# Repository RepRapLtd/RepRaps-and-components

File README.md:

# RepRaps-and-components
Various designs for RepRaps and bits of them

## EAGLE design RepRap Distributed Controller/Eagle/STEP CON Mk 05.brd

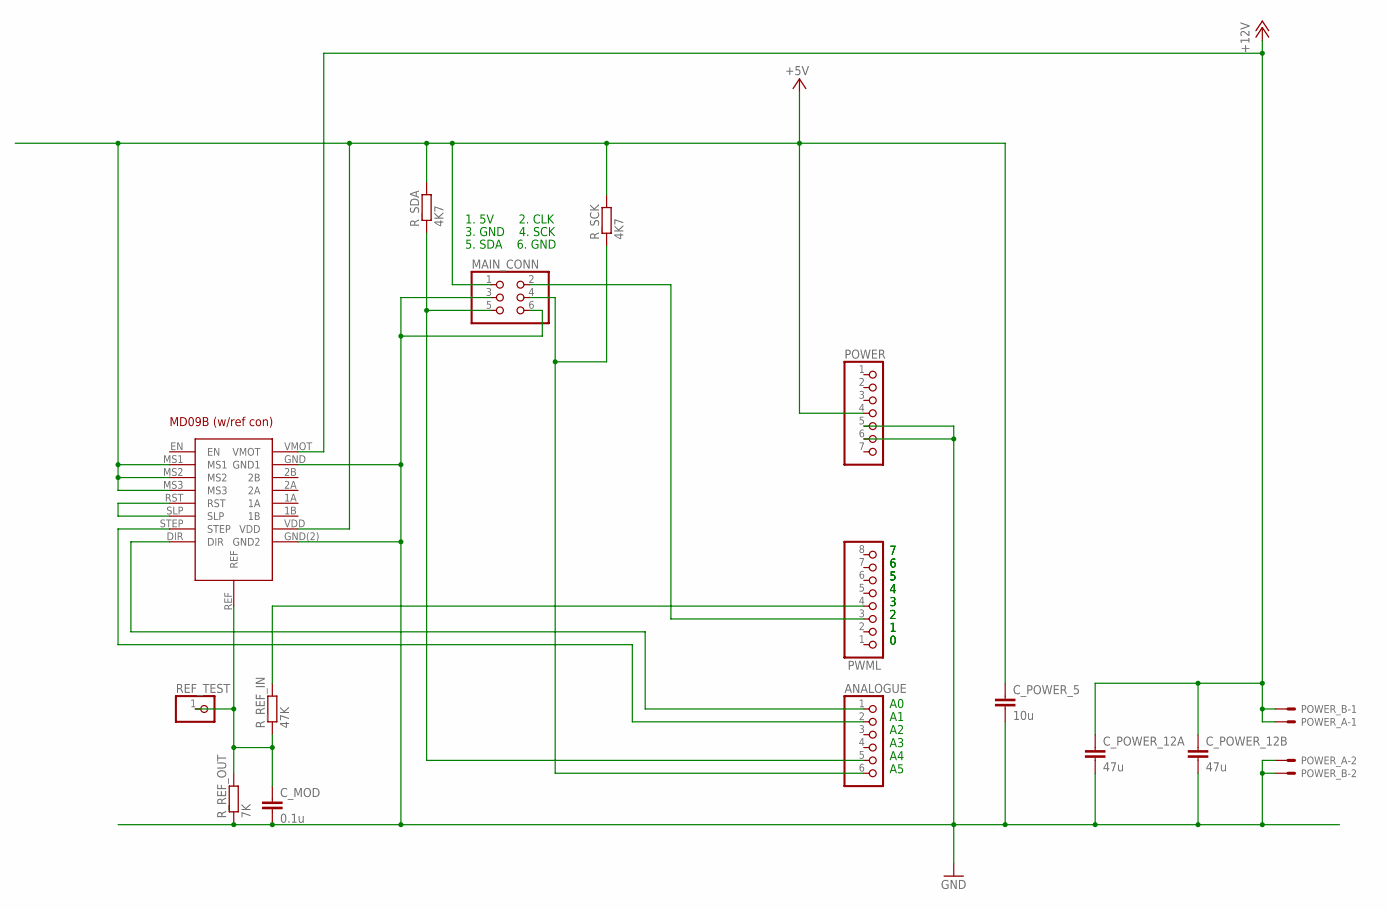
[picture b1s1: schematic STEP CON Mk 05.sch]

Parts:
ANALOGUE: PINHD-1X6; 1X06
C_MOD: 0.1u; C1206
C_POWER_5: 10u; C1206
C_POWER_12A, C_POWER_12B: 47u; C1206
MAIN_CONN: PINHD-2X3; 2X03
POWER: PINHD-1X7; 1X07
POWER_A: KK-156-2
POWER_B: KK-156-2
PWML: PINHD-1X8; 1X08
REF_TEST: PINHD-1X1; 1X01
R_REF_IN: 47K; M0805
R_REF_OUT: 7K; M0805
R_SCK: 4K7; M0805
R_SDA: 4K7; M0805
U$1: MD09B_MOD_LP; MD90B_MOD_LP

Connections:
+5V: C_POWER_5.1, MAIN_CONN.1, POWER.4, R_SCK.2, R_SDA.2, U$1.MS1, U$1.MS2, U$1.MS3, U$1.VDD
+12V: C_POWER_12A.1, C_POWER_12B.1, POWER_A.1, POWER_B.1, U$1.VMOT
DIR: ANALOGUE.1, U$1.DIR
GND: C_MOD.2, C_POWER_5.2, C_POWER_12A.2, C_POWER_12B.2, MAIN_CONN.3, MAIN_CONN.6, POWER.5, POWER.6, POWER_A.2, POWER_B.2, R_REF_OUT.1, U$1.GND (GND1), U$1.GND(2) (GND2)
PWM: PWML.4, R_REF_IN.2
REF1: C_MOD.1, REF_TEST.1, R_REF_IN.1, R_REF_OUT.2, U$1.REF
SCK: ANALOGUE.6, MAIN_CONN.4, R_SCK.1
SDA: ANALOGUE.5, MAIN_CONN.5, R_SDA.1
SKYCLOCK: MAIN_CONN.2, PWML.3
SLP-RST: U$1.RST, U$1.SLP
STEP: ANALOGUE.2, U$1.STEP

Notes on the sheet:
1. 5V 2. CLK 3. GND 4. SCK 5. SDA 6. GND
A0 A1 A2 A3 A4 A5

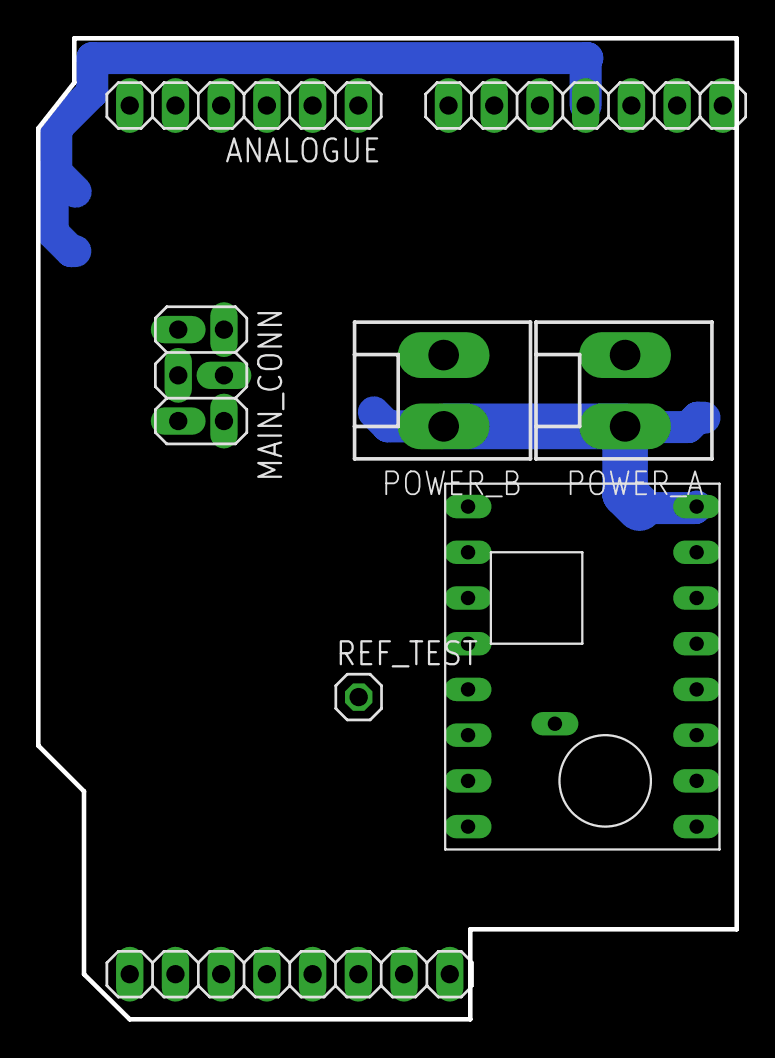
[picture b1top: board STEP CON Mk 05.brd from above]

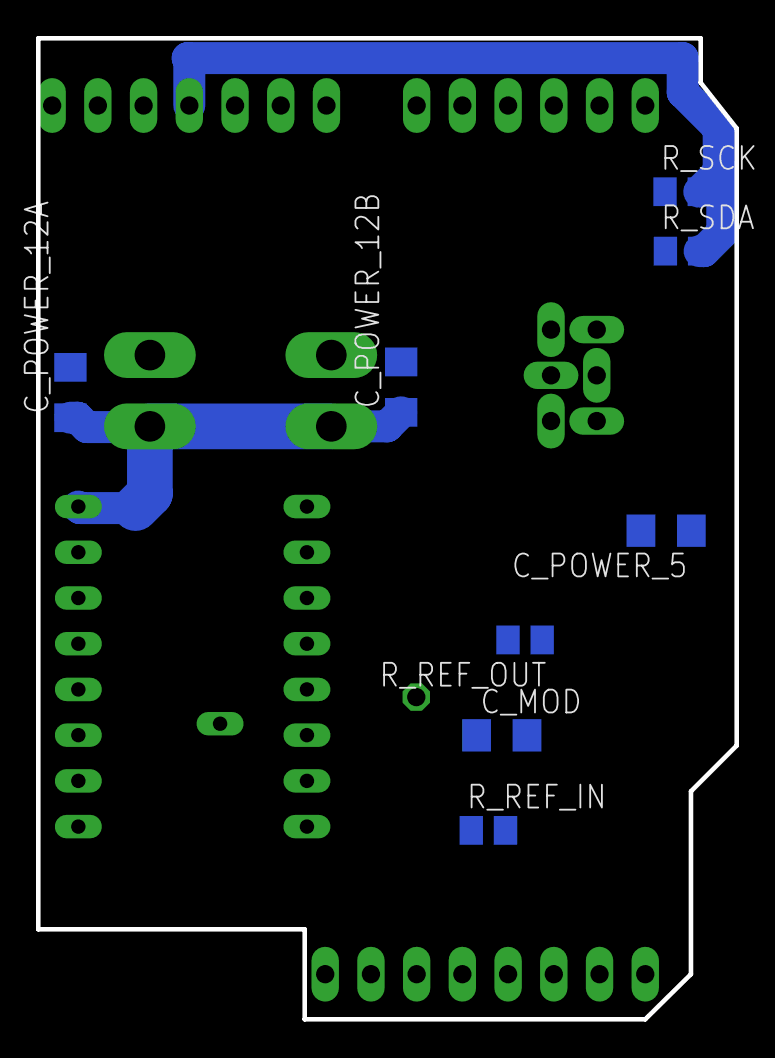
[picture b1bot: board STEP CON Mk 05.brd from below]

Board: 2 copper layers, 38.8 x 54.5 mm, 16 parts (8 on the bottom side), 11 nets.

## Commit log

2024-05-29 Updating...
